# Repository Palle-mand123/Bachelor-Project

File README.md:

# Testbench Bachelor-Project 
Repository for all files in relation to the bachelor project

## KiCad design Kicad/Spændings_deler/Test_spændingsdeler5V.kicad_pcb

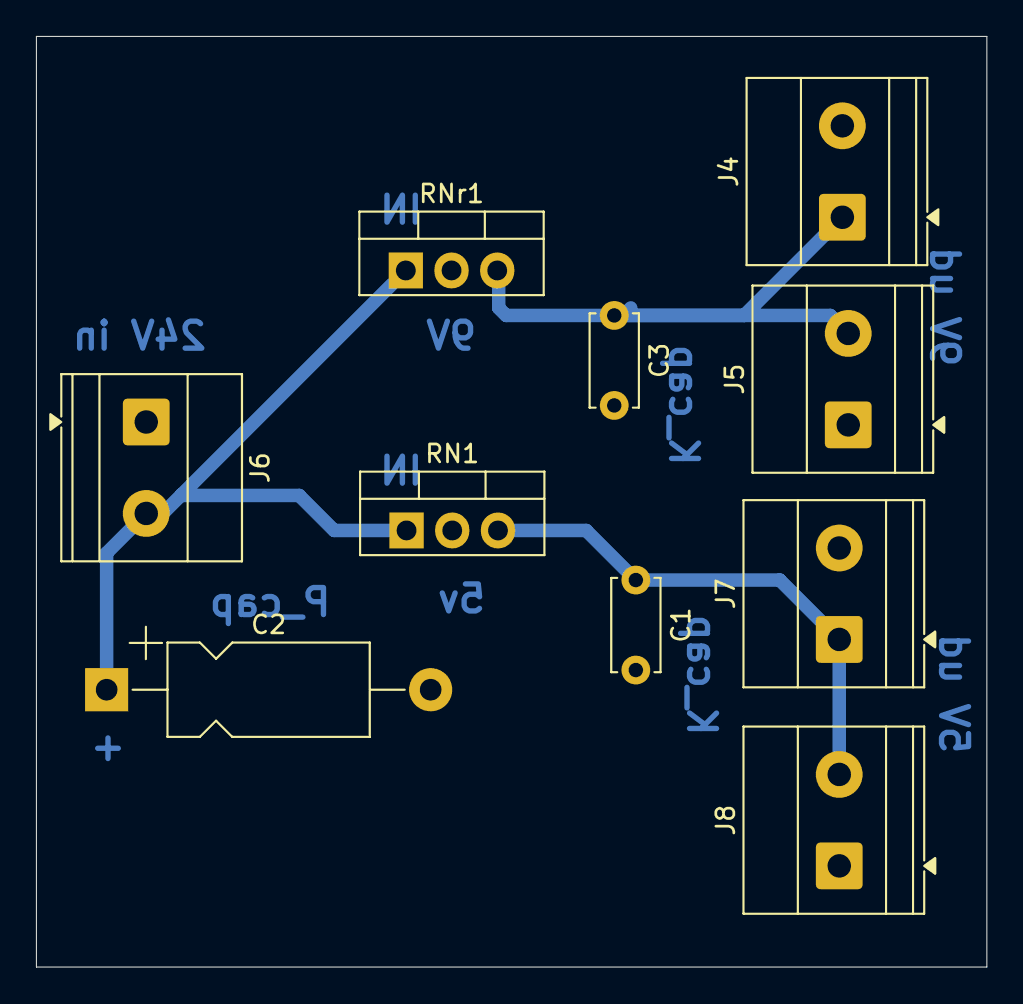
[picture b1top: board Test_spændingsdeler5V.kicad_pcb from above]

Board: 2 copper layers, 52.8 x 51.7 mm, 10 parts (0 on the bottom side), 4 nets.

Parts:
C1, C3: Kermaisk_cap; C_Disc_D5.0mm_W2.5mm_P5.00mm
C2: Polarisede_cap; CP_Axial_L11.0mm_D5.0mm_P18.00mm_Horizontal
J4, J5, J6, J7, J8: Screw_Terminal_01x02; TerminalBlock_Phoenix_MKDS-1,5-2-5.08_1x02_P5.08mm_Horizont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
RN1: 5V_div; TO-220-3_Vertical
RNr1: 9V_div; TO-220-3_Vertical

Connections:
/5V: C1.1, J7.1, J8.2, RN1.3 (OUT)
GND: C1.2, C2.2, C3.2, J4.2, J5.1, J6.1, J7.2, J8.1, RN1.2 (GND), RNr1.2 (GND)
unnamed: C3.1, J4.1, J5.2, RNr1.3 (OUT)
unnamed: C2.1, J6.2, RN1.1 (IN), RNr1.1 (IN)

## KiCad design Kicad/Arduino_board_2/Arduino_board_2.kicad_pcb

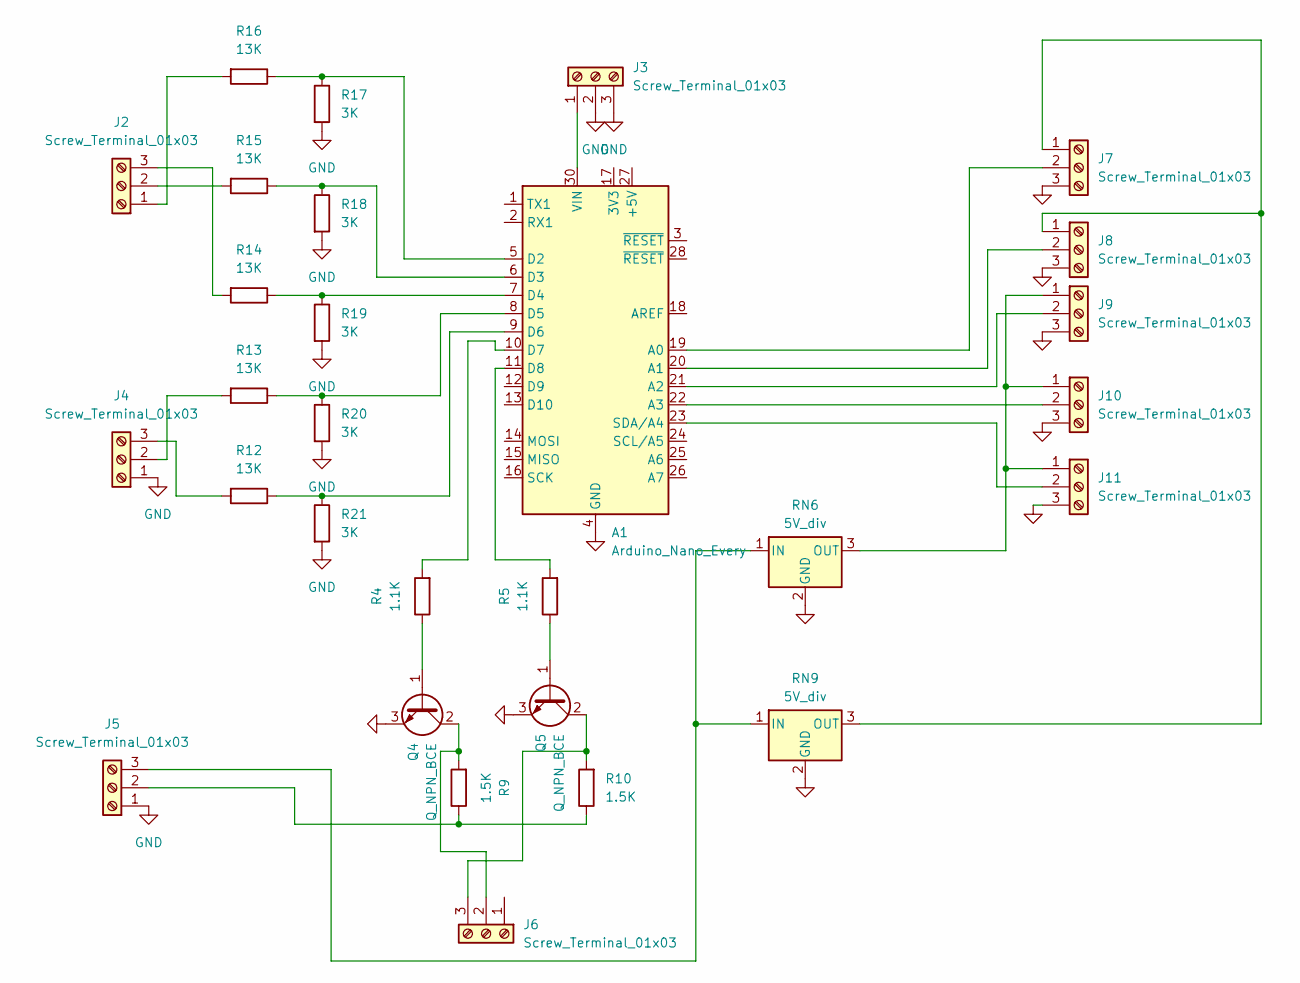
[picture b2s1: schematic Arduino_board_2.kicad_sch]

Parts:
A1: Arduino_Nano_Every; Arduino_Nano
J2, J3, J4, J5, J6, J7, J8, J9, J10, J11: Screw_Terminal_01x03; TerminalBlock_Phoenix_MKDS-1,5-3-5.08_1x03_P5.08mm_Horizont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
Q4, Q5: Q_NPN_BCE; TO-220-3_Vertical
R4, R5: 1.1K; R_Axial_DIN0204_L3.6mm_D1.6mm_P7.62mm_Horizontal
R9, R10: 1.5K; R_Axial_DIN0204_L3.6mm_D1.6mm_P7.62mm_Horizontal
R12, R13, R14, R15, R16: 13K; R_Axial_DIN0204_L3.6mm_D1.6mm_P7.62mm_Horizontal
R17, R18, R19, R20, R21: 3K; R_Axial_DIN0204_L3.6mm_D1.6mm_P7.62mm_Horizontal
RN6, RN9: 5V_div; TO-220-3_Vertical

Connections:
GND: A1.4 (GND), A1.29 (GND), J3.2, J3.3, J4.1, J5.1, J7.3, J8.3, J9.3, J10.3, J11.3, Q4.3 (E), Q5.3 (E), R17.2, R18.2, R19.2, R20.2, R21.2, RN6.2 (GND), RN9.2 (GND)
unnamed: A1.19 (A0), J7.2
unnamed: A1.20 (A1), J8.2
unnamed: A1.21 (A2), J9.2
unnamed: A1.22 (A3), J10.2
unnamed: A1.5 (D2), R16.1, R17.1
unnamed: A1.6 (D3), R15.1, R18.1
unnamed: A1.7 (D4), R14.1, R19.1
unnamed: A1.8 (D5), R13.1, R20.1
unnamed: A1.9 (D6), R12.1, R21.1
unnamed: A1.10 (D7), R4.2
unnamed: A1.11 (D8), R5.2
unnamed: A1.23 (SDA/A4), J11.2
unnamed: A1.30 (VIN), J3.1
unnamed: J2.1, R16.2
unnamed: J2.2, R15.2
unnamed: J2.3, R14.2
unnamed: J4.2, R13.2
unnamed: J4.3, R12.2
unnamed: J5.2, R9.1, R10.1
unnamed: J5.3, RN6.1 (IN), RN9.1 (IN)
unnamed: J6.2, Q4.2 (C), R9.2
unnamed: J6.3, Q5.2 (C), R10.2
unnamed: J7.1, J8.1, RN9.3 (OUT)
unnamed: J9.1, J10.1, J11.1, RN6.3 (OUT)
unnamed: Q4.1 (B), R4.1
unnamed: Q5.1 (B), R5.1

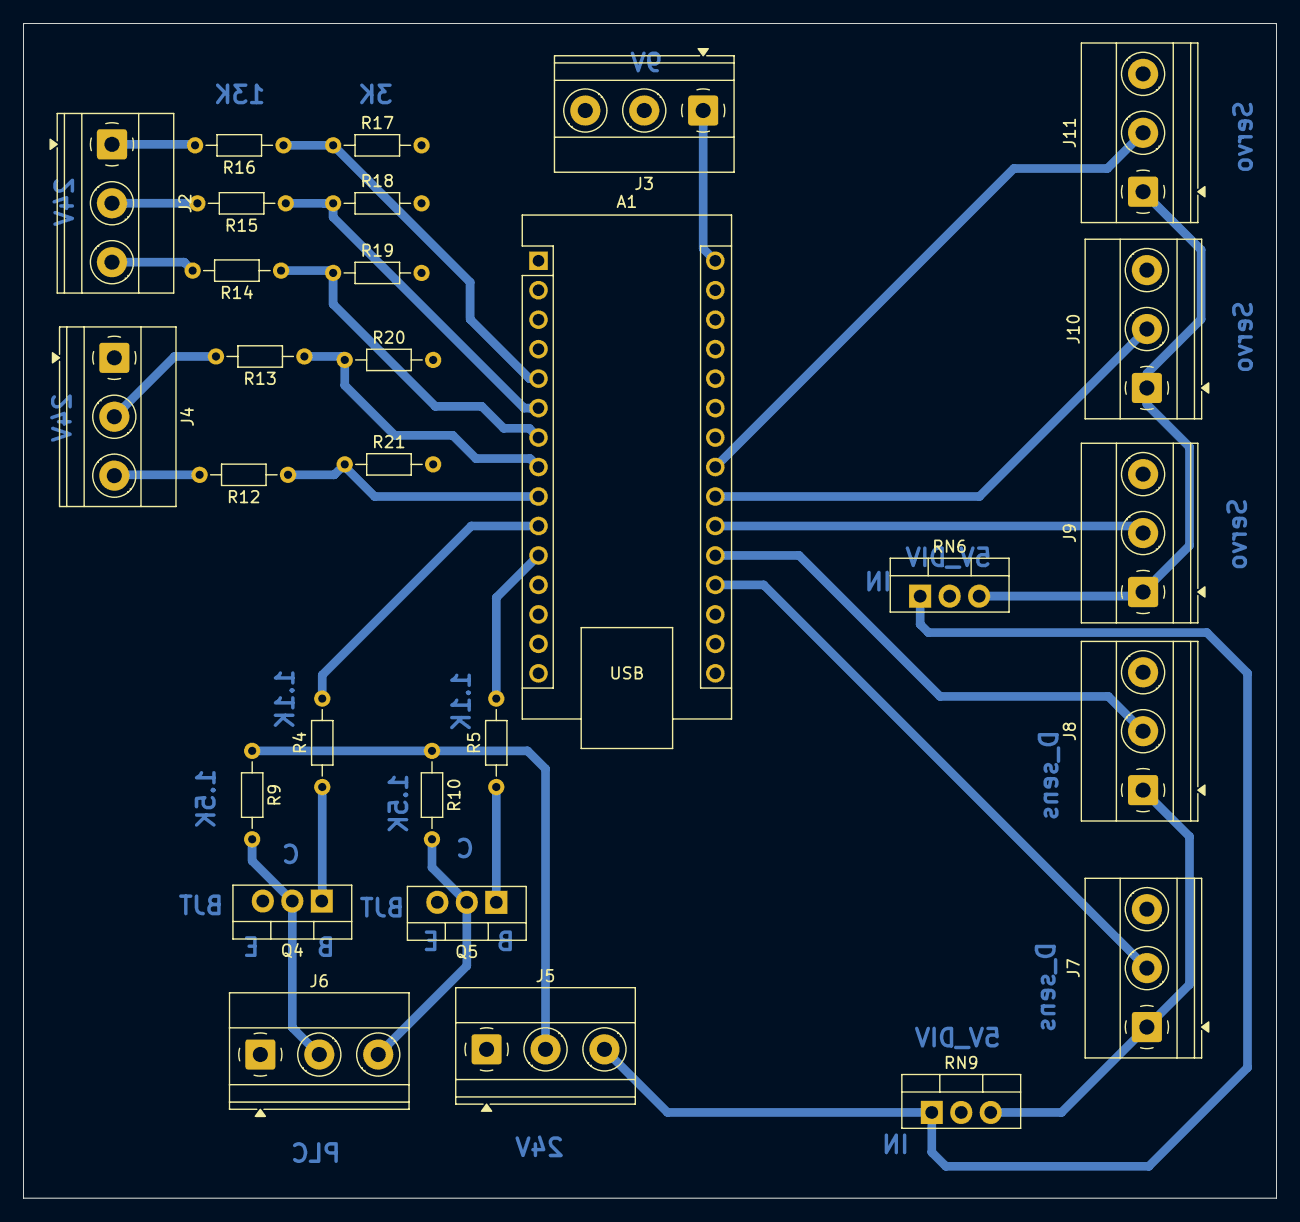
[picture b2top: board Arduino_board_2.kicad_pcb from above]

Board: 2 copper layers, 108.0 x 101.2 mm, 29 parts (0 on the bottom side), 27 nets.

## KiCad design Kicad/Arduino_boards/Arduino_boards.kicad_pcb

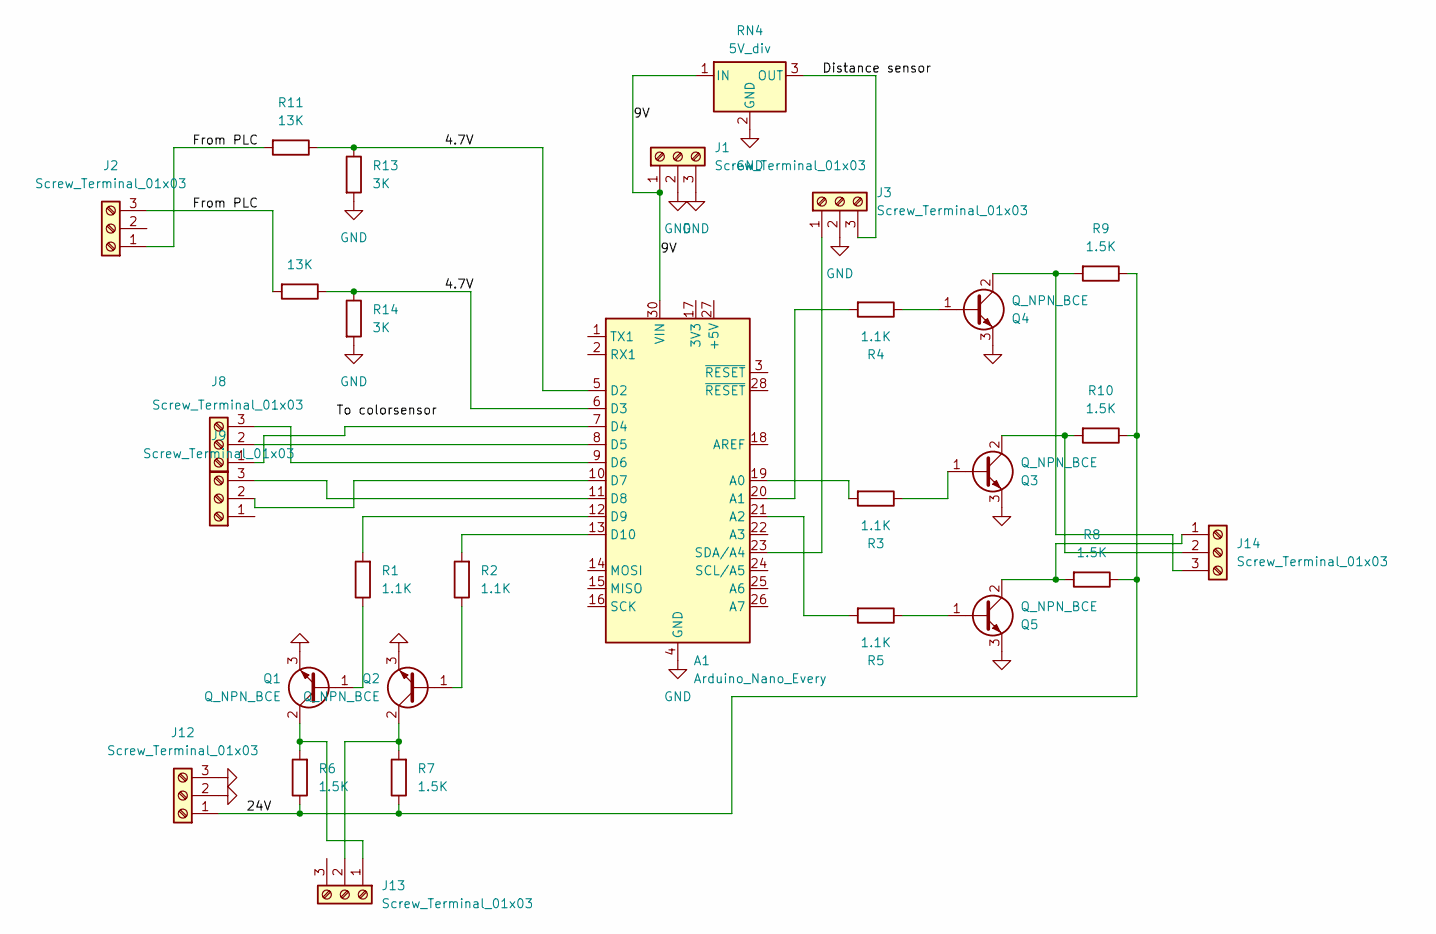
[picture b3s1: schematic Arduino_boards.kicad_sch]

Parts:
A1: Arduino_Nano_Every; Arduino_Nano
J1, J2, J3, J8, J9, J12, J13, J14: Screw_Terminal_01x03; TerminalBlock_Phoenix_MKDS-1,5-3-5.08_1x03_P5.08mm_Horizont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
Q1, Q2, Q3, Q4, Q5: Q_NPN_BCE; TO-220-3_Vertical
R1, R2, R3, R4, R5: 1.1K; R_Axial_DIN0204_L3.6mm_D1.6mm_P7.62mm_Horizontal
R6, R7, R8, R9, R10: 1.5K; R_Axial_DIN0204_L3.6mm_D1.6mm_P7.62mm_Horizontal
R11, R12: 13K; R_Axial_DIN0204_L3.6mm_D1.6mm_P7.62mm_Horizontal
R13, R14: 3K; R_Axial_DIN0204_L3.6mm_D1.6mm_P7.62mm_Horizontal
RN4: 5V_div; TO-220-3_Vertical

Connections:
/4.7V: A1.5 (D2), A1.6 (D3), R11.1, R12.1, R13.1, R14.1
/9V: A1.30 (VIN), J1.1, RN4.1 (IN)
/24V: J12.1, R6.1, R7.1, R8.1, R9.1, R10.1
/Distance sensor: J3.3, RN4.3 (OUT)
/From PLC: J2.1, J2.3, R11.2, R12.2
GND: A1.4 (GND), A1.29 (GND), J1.2, J1.3, J3.2, J12.2, J12.3, Q1.3 (E), Q2.3 (E), Q3.3 (E), Q4.3 (E), Q5.3 (E), R13.2, R14.2, RN4.2 (GND)
unnamed: A1.19 (A0), R3.2
unnamed: A1.20 (A1), R4.2
unnamed: A1.21 (A2), R5.2
unnamed: A1.7 (D4), J8.1
unnamed: A1.8 (D5), J8.2
unnamed: A1.9 (D6), J8.3
unnamed: A1.10 (D7), J9.2
unnamed: A1.11 (D8), J9.3
unnamed: A1.12 (D9), R1.2
unnamed: A1.13 (D10), R2.2
unnamed: A1.23 (SDA/A4), J3.1
unnamed: J13.1, Q1.2 (C), R6.2
unnamed: J13.2, Q2.2 (C), R7.2
unnamed: J14.1, Q5.2 (C), R8.2
unnamed: J14.2, Q3.2 (C), R10.2
unnamed: J14.3, Q4.2 (C), R9.2
unnamed: Q1.1 (B), R1.1
unnamed: Q2.1 (B), R2.1
unnamed: Q3.1 (B), R3.1
unnamed: Q4.1 (B), R4.1
unnamed: Q5.1 (B), R5.1

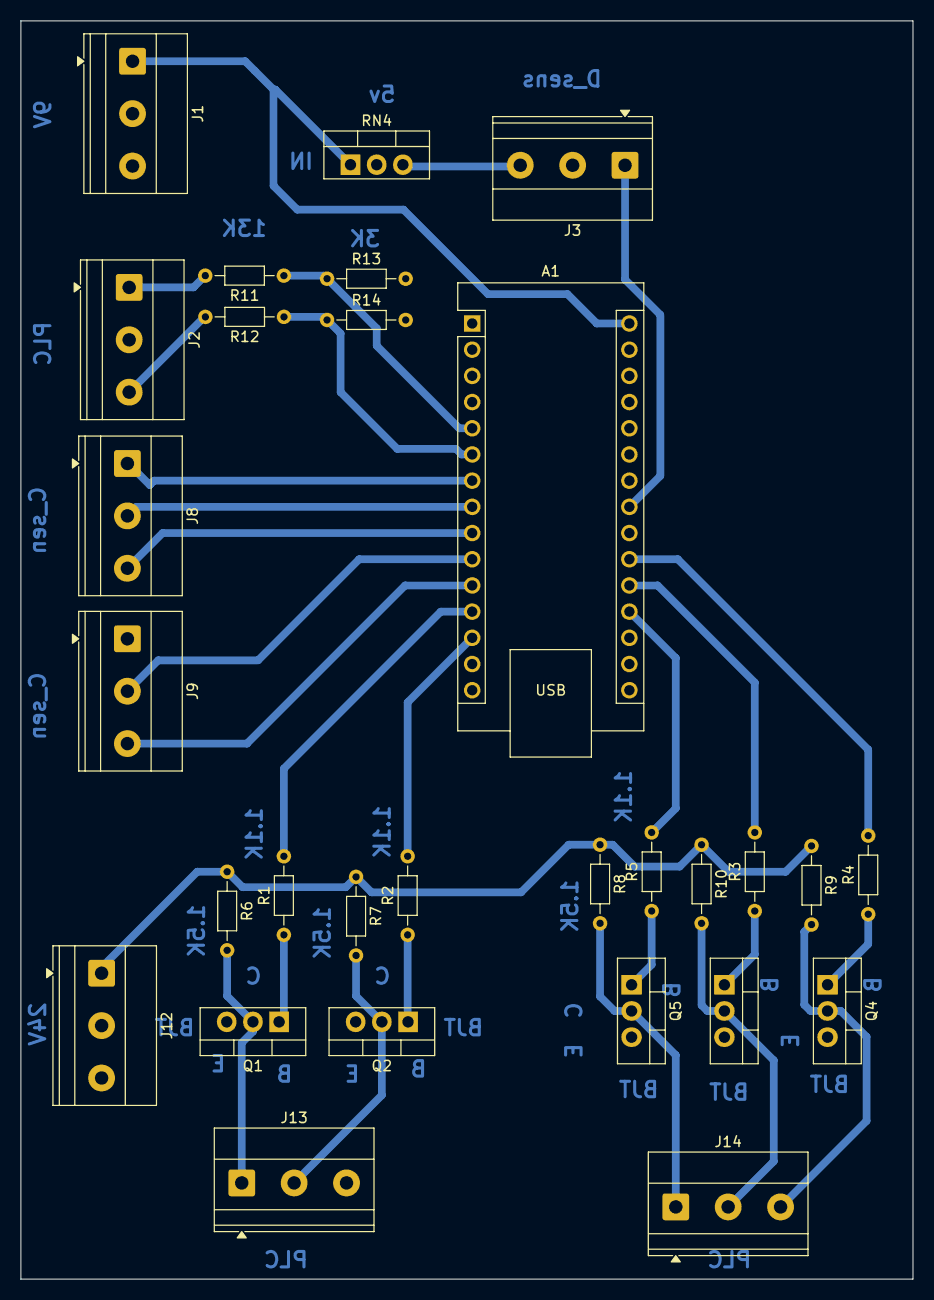
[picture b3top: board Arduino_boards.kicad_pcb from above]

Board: 2 copper layers, 86.5 x 122.0 mm, 29 parts (0 on the bottom side), 27 nets.

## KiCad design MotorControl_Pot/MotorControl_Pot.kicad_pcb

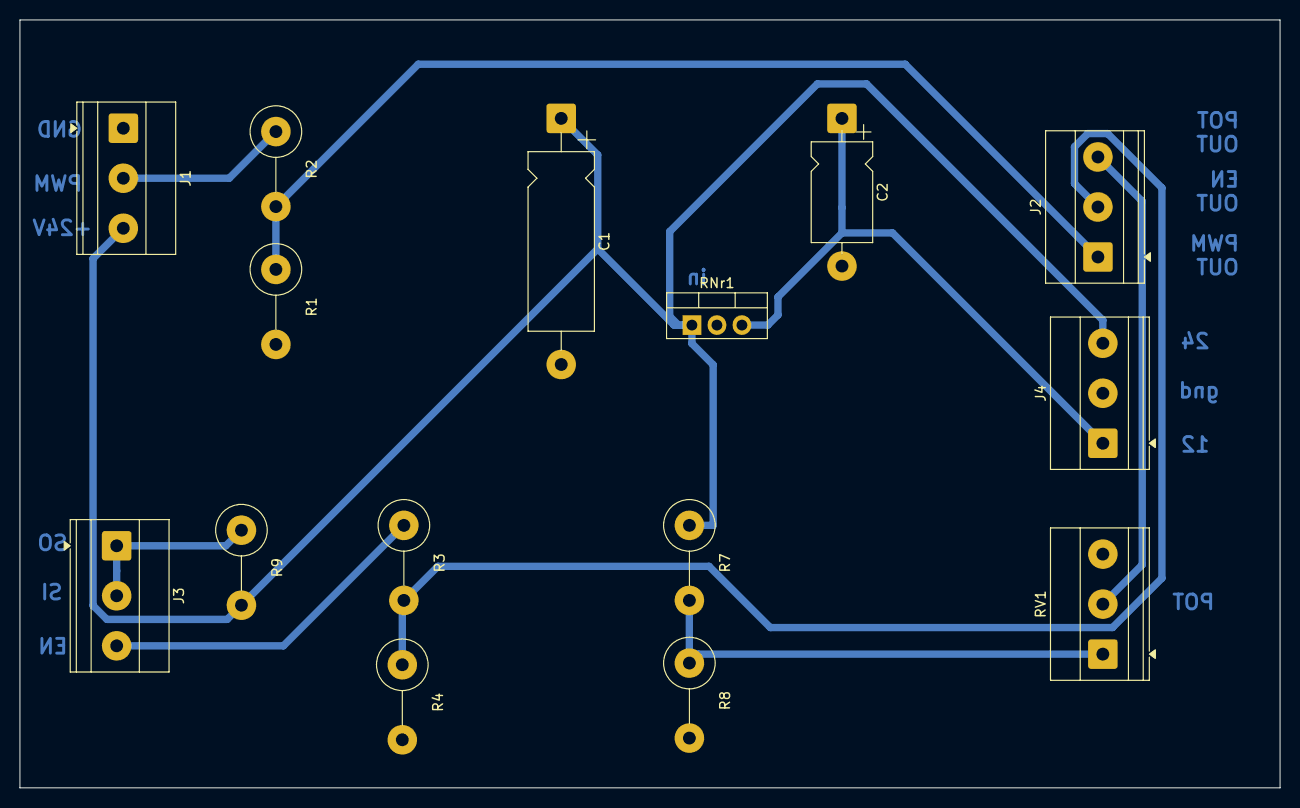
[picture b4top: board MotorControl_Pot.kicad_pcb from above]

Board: 2 copper layers, 128.0 x 78.0 mm, 15 parts (0 on the bottom side), 10 nets.

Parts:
C1: C; CP_Axial_L18.0mm_D6.5mm_P25.00mm_Horizontal
C2: C; CP_Axial_L10.0mm_D6.0mm_P15.00mm_Horizontal
J1, J2, J3: Input; TerminalBlock_Phoenix_MKDS-1,5-3-5.08_1x03_P5.08mm_Horizont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
J4: H-Bridge; TerminalBlock_Phoenix_MKDS-1,5-3-5.08_1x03_P5.08mm_Horizont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
R1: 4,7k / 5,5k; R_Axial_DIN0516_L15.5mm_D5.0mm_P7.62mm_Vertical
R2, R3: 18k/22k; R_Axial_DIN0516_L15.5mm_D5.0mm_P7.62mm_Vertical
R4: 4,7k / 5,6k; R_Axial_DIN0516_L15.5mm_D5.0mm_P7.62mm_Vertical
R7: 5,6k; R_Axial_DIN0516_L15.5mm_D5.0mm_P7.62mm_Vertical
R8, R9: 10k; R_Axial_DIN0516_L15.5mm_D5.0mm_P7.62mm_Vertical
RNr1: 12V_div; TO-220-3_Vertical
RV1: R_Potentiometer; TerminalBlock_Phoenix_MKDS-1,5-3-5.08_1x03_P5.08mm_Horizont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

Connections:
+24V: C1.1, J1.3, J4.3, R7.1, R9.2, RNr1.1 (IN)
/ENABLE: J3.3, R3.1
/ENABLE_5V: J2.2, R3.2, R4.1
/H_12V: C2.1, J4.1, RNr1.3 (OUT)
/Indu_Sens: J3.1, J3.2, R9.1
/POT: J2.3, RV1.2
/PWM: J1.2, R2.1
/PWM_5V: J2.1, R1.1, R2.2
GND: C1.2, C2.2, J1.1, J4.2, R1.2, R4.2, R8.2, RNr1.2 (GND), RV1.3
unnamed: R7.2, R8.1, RV1.1

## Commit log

2025-05-23 Create 3D-prints
    Here we have all the 3D part and print files
2025-05-23 3D-Designs directory
